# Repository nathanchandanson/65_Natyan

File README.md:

# 65_Natyan

The 65_Natyan is a custom 65% mechanical keyboard. It has individually addressable SK6812 led under each key. It is hotswappable and support both Cherry MX and Kailh Choc switches.

# Work in progress

This project is currently being developed, thus it is not sure that all will work.

## PCB

The Kicad project is accessible in the folder "pcb_files". You can open it to export the GERBER files and then order the PCB.

## Firmware

The firmware is based on [qmk_firmware](https://github.com/qmk/qmk_firmware). To flash the firmware, just follow the instructions given on the QMK docs.

## 3dModels

You can find the 3d models of the case I designed for this keyboard. 
To get it, you need to 3d print them, and wherever there is a hole for a fastener, you need to install a heat-press insert.

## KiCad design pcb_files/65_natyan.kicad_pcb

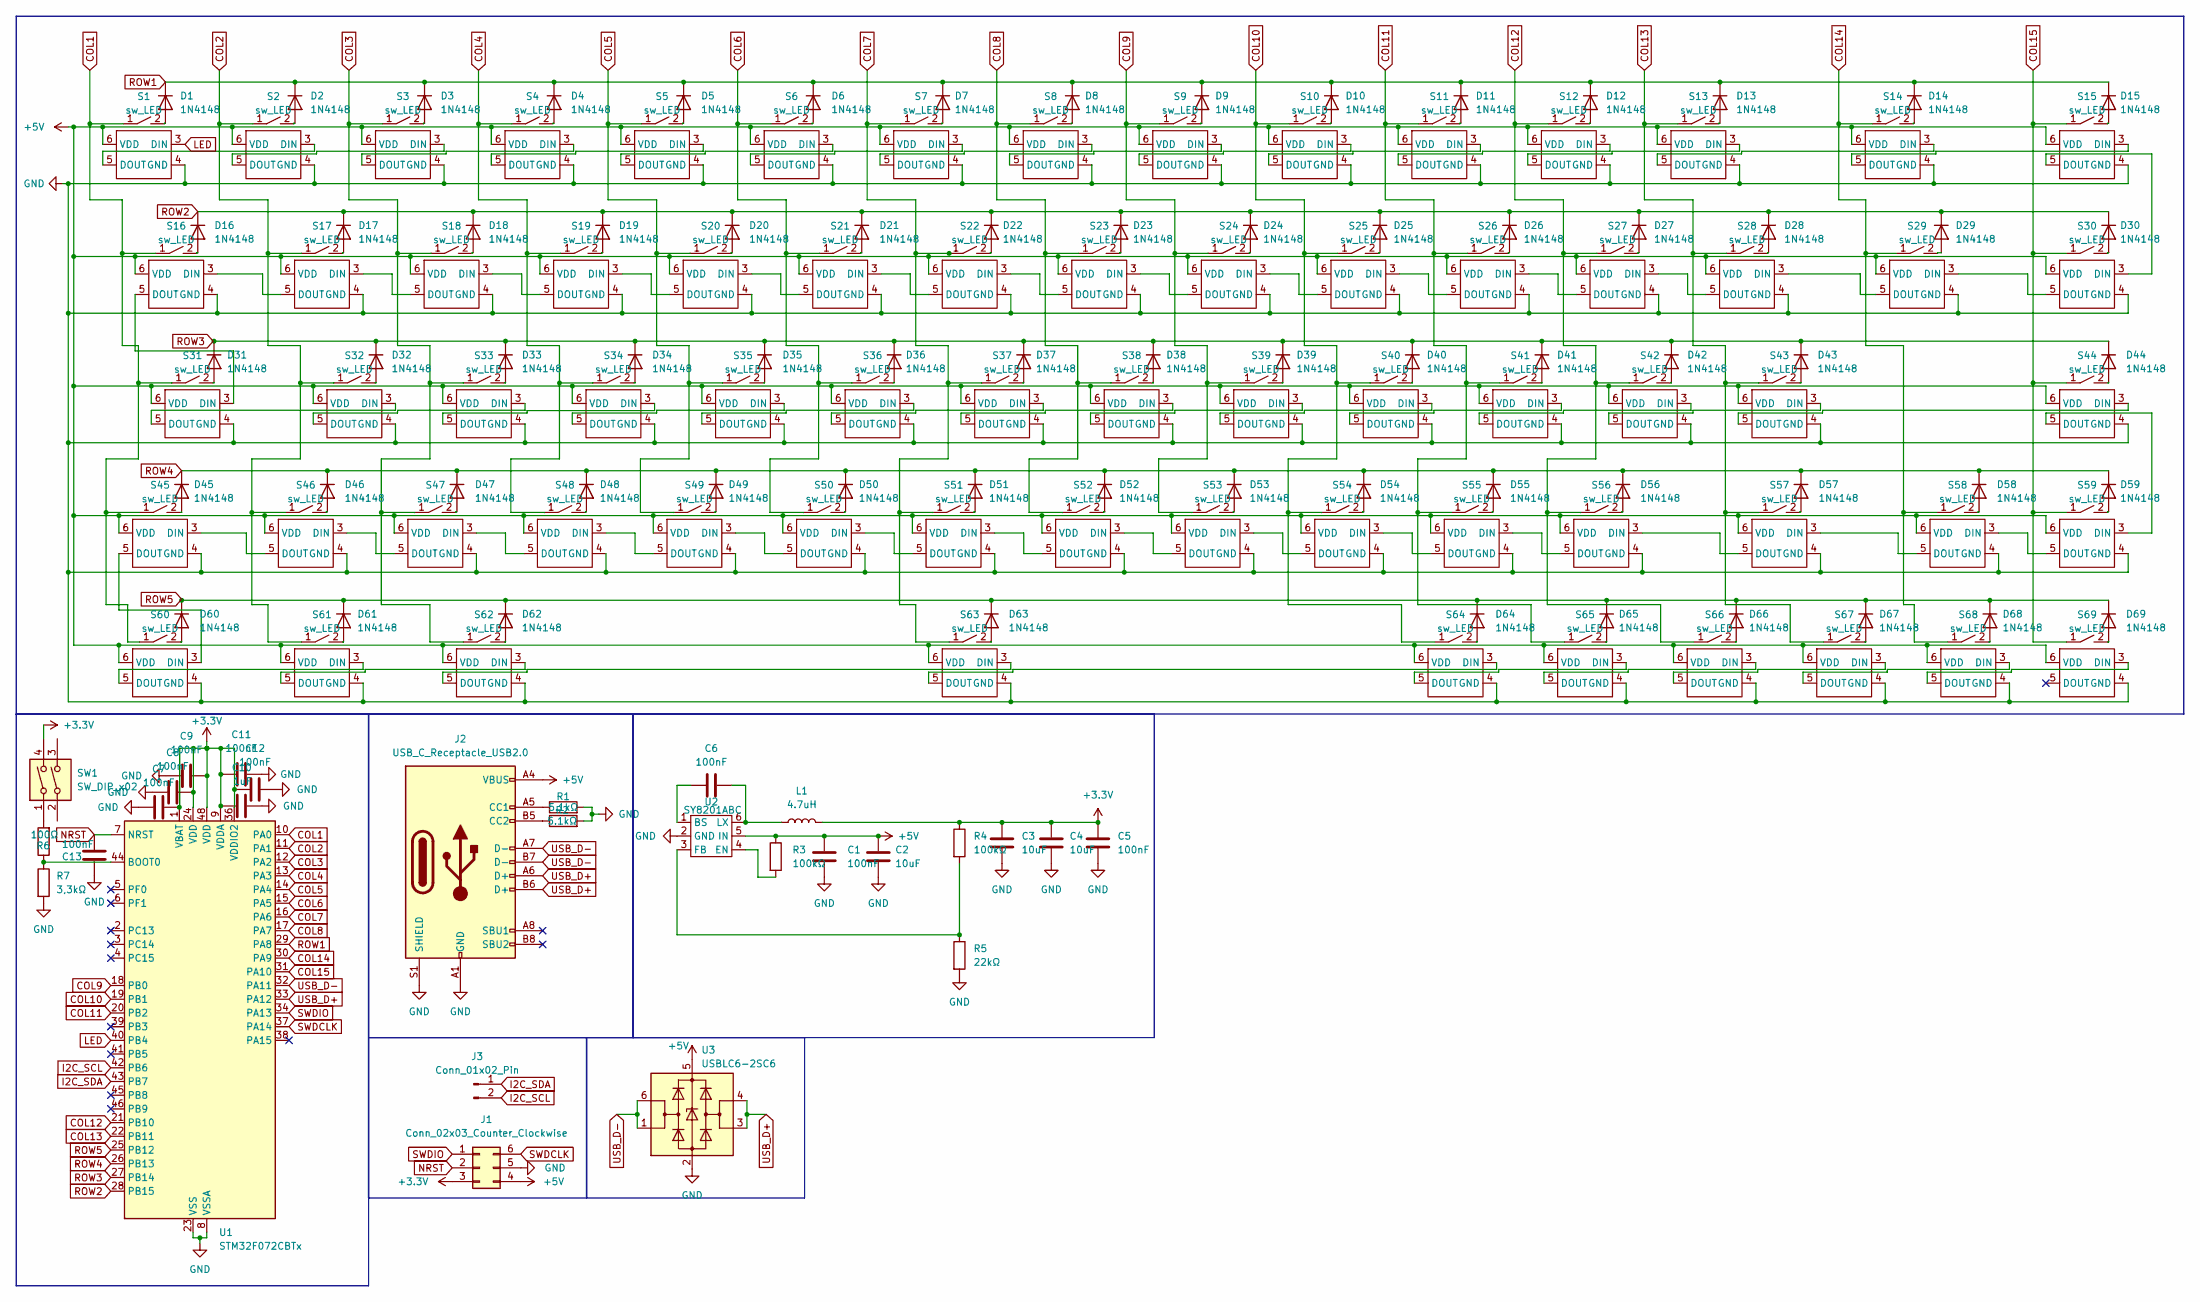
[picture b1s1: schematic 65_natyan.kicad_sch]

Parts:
C1, C5, C6, C7, C8, C9, C11, C12, C13: 100nF; C_0603_1608Metric_Pad1.08x0.95mm_HandSolder
C2, C3, C4: 10uF; C_0603_1608Metric_Pad1.08x0.95mm_HandSolder
C10: 1uF; C_0603_1608Metric_Pad1.08x0.95mm_HandSolder
D1, D2, D3, D4, D5, D6, D7, D8, D9, D10, D11, D12, D13, D14, D15, D16, D17, D18, D19, D20, D21, D22, D23, D24, D25, D26, D27, D28, D29, D30, D31, D32, D33, D34, D35, D36, D37, D38, D39, D40, D41, D42, D43, D44, D45, D46, D47, D48, D49, D50, D51, D52, D53, D54, D55, D56, D57, D58, D59, D60, D61, D62, D63, D64, D65, D66, D67, D68, D69: 1N4148; D_DO-35_SOD27_P7.62mm_Horizontal
J1: Conn_02x03_Counter_Clockwise; PinHeader_2x03_P2.54mm_Vertical
J2: USB_C_Receptacle_USB2.0; USB-C-SMD_KH-TYPE-C-16P
J3: Conn_01x02_Pin; PinHeader_1x02_P2.54mm_Vertical
L1: 4.7uH; L_0603_1608Metric_Pad1.05x0.95mm_HandSolder
R1, R2: 5.1kΩ; R_0603_1608Metric_Pad0.98x0.95mm_HandSolder
R3, R4: 100kΩ; R_0603_1608Metric_Pad0.98x0.95mm_HandSolder
R5: 22kΩ; R_0603_1608Metric_Pad0.98x0.95mm_HandSolder
R6: 100Ω; R_0603_1608Metric_Pad0.98x0.95mm_HandSolder
R7: 3,3kΩ; R_0603_1608Metric_Pad0.98x0.95mm_HandSolder
S1, S2, S3, S4, S5, S6, S7, S8, S9, S10, S11, S12, S13, S15, S17, S18, S19, S20, S21, S22, S23, S24, S25, S26, S27, S28, S30, S32, S33, S34, S35, S36, S37, S38, S39, S40, S41, S42, S43, S44, S46, S47, S48, S49, S50, S51, S52, S53, S54, S55, S56, S58, S59, S64, S65, S66, S67, S68, S69: sw_LED; sw_MX-Choc_Hotswap-underLED_1u
S14: sw_LED; sw_MX-Choc_Hotswap-underLED_2u
S16: sw_LED; sw_MX-Choc_Hotswap-underLED_1.5u
S29: sw_LED; sw_MX-Choc_Hotswap-underLED_isoEnter
S31, S57: sw_LED; sw_MX-Choc_Hotswap-underLED_1.75u
S45, S60, S61, S62: sw_LED; sw_MX-Choc_Hotswap-underLED_1.25u
S63: sw_LED; sw_MX-Choc_Hotswap-underLED_6,25u
SW1: SW_DIP_x02; rst_sw
U1: STM32F072CBTx; LQFP-48_7x7mm_P0.5mm
U2: SY8201ABC; SOT-23-6_Handsoldering
U3: USBLC6-2SC6; SOT-23-6_Handsoldering

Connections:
+3.3V: C3.1, C4.1, C5.1, C7.2, C8.1, C9.2, C10.1, C11.1, C12.1, J1.3, L1.2, R4.1, SW1.4, U1.1 (VBAT), U1.9 (VDDA), U1.24 (VDD), U1.36 (VDDIO2), U1.48 (VDD)
+5V: C1.1, C2.1, J1.4, J2.A4 (VBUS), J2.A9 (VBUS), J2.B4 (VBUS), J2.B9 (VBUS), R3.1, S1.6 (VDD), S2.6 (VDD), S3.6 (VDD), S4.6 (VDD), S5.6 (VDD), S6.6 (VDD), S7.6 (VDD), S8.6 (VDD), S9.6 (VDD), S10.6 (VDD), S11.6 (VDD), S12.6 (VDD), S13.6 (VDD), S14.6 (VDD), S15.6 (VDD), S16.6 (VDD), S17.6 (VDD), S18.6 (VDD), S19.6 (VDD), S20.6 (VDD), S21.6 (VDD), S22.6 (VDD), S23.6 (VDD), S24.6 (VDD), S25.6 (VDD), S26.6 (VDD), S27.6 (VDD), S28.6 (VDD), S29.6 (VDD), S30.6 (VDD), S31.6 (VDD), S32.6 (VDD), S33.6 (VDD), S34.6 (VDD), S35.6 (VDD), S36.6 (VDD), S37.6 (VDD), S38.6 (VDD), S39.6 (VDD), S40.6 (VDD), S41.6 (VDD), S42.6 (VDD), S43.6 (VDD), S44.6 (VDD), S45.6 (VDD), S46.6 (VDD), S47.6 (VDD), S48.6 (VDD), S49.6 (VDD), S50.6 (VDD), S51.6 (VDD), S52.6 (VDD), S53.6 (VDD), S54.6 (VDD), S55.6 (VDD), S56.6 (VDD), S57.6 (VDD), S58.6 (VDD), S59.6 (VDD), S60.6 (VDD), S61.6 (VDD), S62.6 (VDD), S63.6 (VDD), S64.6 (VDD), S65.6 (VDD), S66.6 (VDD), S67.6 (VDD), S68.6 (VDD), S69.6 (VDD), U2.5 (IN), U3.5 (VBUS)
COL1: S1.1, S16.1, S31.1, S45.1, S60.1, U1.10 (PA0)
COL2: S2.1, S17.1, S32.1, S46.1, S61.1, U1.11 (PA1)
COL3: S3.1, S18.1, S33.1, S47.1, S62.1, U1.12 (PA2)
COL4: S4.1, S19.1, S34.1, S48.1, U1.13 (PA3)
COL5: S5.1, S20.1, S35.1, S49.1, U1.14 (PA4)
COL6: S6.1, S21.1, S36.1, S50.1, U1.15 (PA5)
COL7: S7.1, S22.1, S37.1, S51.1, S63.1, U1.16 (PA6)
COL8: S8.1, S23.1, S38.1, S52.1, U1.17 (PA7)
COL9: S9.1, S24.1, S39.1, S53.1, U1.18 (PB0)
COL10: S10.1, S25.1, S40.1, S54.1, S64.1, U1.19 (PB1)
COL11: S11.1, S26.1, S41.1, S55.1, S65.1, U1.20 (PB2)
COL12: S12.1, S27.1, S42.1, S56.1, S66.1, U1.21 (PB10)
COL13: S13.1, S28.1, S43.1, S57.1, S67.1, U1.22 (PB11)
COL14: S14.1, S29.1, S58.1, S68.1, U1.30 (PA9)
COL15: S15.1, S30.1, S44.1, S59.1, S69.1, U1.31 (PA10)
GND: C1.2, C2.2, C3.2, C4.2, C5.2, C7.1, C8.2, C9.1, C10.2, C11.2, C12.2, C13.1, J1.5, J2.A1 (GND), J2.A12 (GND), J2.B1 (GND), J2.B12 (GND), J2.S1 (SHIELD), R1.2, R2.2, R5.2, R7.2, S1.4 (GND), S2.4 (GND), S3.4 (GND), S4.4 (GND), S5.4 (GND), S6.4 (GND), S7.4 (GND), S8.4 (GND), S9.4 (GND), S10.4 (GND), S11.4 (GND), S12.4 (GND), S13.4 (GND), S14.4 (GND), S15.4 (GND), S16.4 (GND), S17.4 (GND), S18.4 (GND), S19.4 (GND), S20.4 (GND), S21.4 (GND), S22.4 (GND), S23.4 (GND), S24.4 (GND), S25.4 (GND), S26.4 (GND), S27.4 (GND), S28.4 (GND), S29.4 (GND), S30.4 (GND), S31.4 (GND), S32.4 (GND), S33.4 (GND), S34.4 (GND), S35.4 (GND), S36.4 (GND), S37.4 (GND), S38.4 (GND), S39.4 (GND), S40.4 (GND), S41.4 (GND), S42.4 (GND), S43.4 (GND), S44.4 (GND), S45.4 (GND), S46.4 (GND), S47.4 (GND), S48.4 (GND), S49.4 (GND), S50.4 (GND), S51.4 (GND), S52.4 (GND), S53.4 (GND), S54.4 (GND), S55.4 (GND), S56.4 (GND), S57.4 (GND), S58.4 (GND), S59.4 (GND), S60.4 (GND), S61.4 (GND), S62.4 (GND), S63.4 (GND), S64.4 (GND), S65.4 (GND), S66.4 (GND), S67.4 (GND), S68.4 (GND), S69.4 (GND), U1.8 (VSSA), U1.23 (VSS), U1.35 (VSS), U1.47 (VSS), U2.2 (GND), U3.2 (GND)
I2C_SCL: J3.2, U1.42 (PB6)
I2C_SDA: J3.1, U1.43 (PB7)
LED: S1.3 (DIN), U1.40 (PB4)
NRST: C13.2, J1.2, U1.7 (NRST)
unnamed: D1.2 (A), S1.2
unnamed: D2.2 (A), S2.2
unnamed: D3.2 (A), S3.2
unnamed: D4.2 (A), S4.2
unnamed: D5.2 (A), S5.2
unnamed: D6.2 (A), S6.2
unnamed: D7.2 (A), S7.2
unnamed: D8.2 (A), S8.2
unnamed: D9.2 (A), S9.2
unnamed: D10.2 (A), S10.2
unnamed: D11.2 (A), S11.2
unnamed: D12.2 (A), S12.2
unnamed: D13.2 (A), S13.2
unnamed: D14.2 (A), S14.2
unnamed: D15.2 (A), S15.2
unnamed: D16.2 (A), S16.2
unnamed: D17.2 (A), S17.2
unnamed: D18.2 (A), S18.2
unnamed: D19.2 (A), S19.2
unnamed: D20.2 (A), S20.2
unnamed: D21.2 (A), S21.2
unnamed: D22.2 (A), S22.2
unnamed: D23.2 (A), S23.2
unnamed: D24.2 (A), S24.2
unnamed: D25.2 (A), S25.2
unnamed: D26.2 (A), S26.2
unnamed: D27.2 (A), S27.2
unnamed: D28.2 (A), S28.2
unnamed: D29.2 (A), S29.2
unnamed: D30.2 (A), S30.2
unnamed: D31.2 (A), S31.2
unnamed: D32.2 (A), S32.2
unnamed: D33.2 (A), S33.2
unnamed: D34.2 (A), S34.2
unnamed: D35.2 (A), S35.2
unnamed: D36.2 (A), S36.2
unnamed: D37.2 (A), S37.2
unnamed: D38.2 (A), S38.2
unnamed: D39.2 (A), S39.2
unnamed: D40.2 (A), S40.2
unnamed: D41.2 (A), S41.2
unnamed: D42.2 (A), S42.2
unnamed: D43.2 (A), S43.2
unnamed: D44.2 (A), S44.2
unnamed: D45.2 (A), S45.2
unnamed: D46.2 (A), S46.2
unnamed: D47.2 (A), S47.2
unnamed: D48.2 (A), S48.2
unnamed: D49.2 (A), S49.2
unnamed: D50.2 (A), S50.2
unnamed: D51.2 (A), S51.2
unnamed: D52.2 (A), S52.2
unnamed: D53.2 (A), S53.2
unnamed: D54.2 (A), S54.2
unnamed: D55.2 (A), S55.2
unnamed: D56.2 (A), S56.2
unnamed: D57.2 (A), S57.2
unnamed: D58.2 (A), S58.2
unnamed: D59.2 (A), S59.2
unnamed: D60.2 (A), S60.2
unnamed: D61.2 (A), S61.2
unnamed: D62.2 (A), S62.2
unnamed: D63.2 (A), S63.2
unnamed: D64.2 (A), S64.2
unnamed: D65.2 (A), S65.2
unnamed: D66.2 (A), S66.2
unnamed: D67.2 (A), S67.2
unnamed: D68.2 (A), S68.2
unnamed: D69.2 (A), S69.2
unnamed: J2.A5 (CC1), R1.1
unnamed: J2.B5 (CC2), R2.1
unnamed: R6.2, SW1.1
unnamed: S1.5 (DOUT), S2.3 (DIN)
unnamed: S2.5 (DOUT), S3.3 (DIN)
unnamed: S3.5 (DOUT), S4.3 (DIN)
unnamed: S4.5 (DOUT), S5.3 (DIN)
unnamed: S5.5 (DOUT), S6.3 (DIN)
unnamed: S6.5 (DOUT), S7.3 (DIN)
unnamed: S7.5 (DOUT), S8.3 (DIN)
unnamed: S8.5 (DOUT), S9.3 (DIN)
unnamed: S9.5 (DOUT), S10.3 (DIN)
unnamed: S10.5 (DOUT), S11.3 (DIN)
unnamed: S11.5 (DOUT), S12.3 (DIN)
unnamed: S12.5 (DOUT), S13.3 (DIN)
unnamed: S13.5 (DOUT), S14.3 (DIN)
unnamed: S14.5 (DOUT), S15.3 (DIN)
unnamed: S15.5 (DOUT), S30.3 (DIN)
unnamed: S16.3 (DIN), S17.5 (DOUT)
unnamed: S16.5 (DOUT), S31.3 (DIN)
unnamed: S17.3 (DIN), S18.5 (DOUT)
unnamed: S18.3 (DIN), S19.5 (DOUT)
unnamed: S19.3 (DIN), S20.5 (DOUT)
unnamed: S20.3 (DIN), S21.5 (DOUT)
unnamed: S21.3 (DIN), S22.5 (DOUT)
unnamed: S22.3 (DIN), S23.5 (DOUT)
unnamed: S23.3 (DIN), S24.5 (DOUT)
unnamed: S24.3 (DIN), S25.5 (DOUT)
unnamed: S25.3 (DIN), S26.5 (DOUT)
unnamed: S26.3 (DIN), S27.5 (DOUT)
unnamed: S27.3 (DIN), S28.5 (DOUT)
unnamed: S28.3 (DIN), S29.5 (DOUT)
unnamed: S29.3 (DIN), S30.5 (DOUT)
unnamed: S31.5 (DOUT), S32.3 (DIN)
unnamed: S32.5 (DOUT), S33.3 (DIN)
unnamed: S33.5 (DOUT), S34.3 (DIN)
unnamed: S34.5 (DOUT), S35.3 (DIN)
unnamed: S35.5 (DOUT), S36.3 (DIN)
unnamed: S36.5 (DOUT), S37.3 (DIN)
unnamed: S37.5 (DOUT), S38.3 (DIN)
unnamed: S38.5 (DOUT), S39.3 (DIN)
unnamed: S39.5 (DOUT), S40.3 (DIN)
unnamed: S40.5 (DOUT), S41.3 (DIN)
unnamed: S41.5 (DOUT), S42.3 (DIN)
unnamed: S42.5 (DOUT), S43.3 (DIN)
unnamed: S43.5 (DOUT), S44.3 (DIN)
unnamed: S44.5 (DOUT), S59.3 (DIN)
unnamed: S45.3 (DIN), S46.5 (DOUT)
unnamed: S45.5 (DOUT), S60.3 (DIN)
unnamed: S46.3 (DIN), S47.5 (DOUT)
unnamed: S47.3 (DIN), S48.5 (DOUT)
unnamed: S48.3 (DIN), S49.5 (DOUT)
unnamed: S49.3 (DIN), S50.5 (DOUT)
unnamed: S50.3 (DIN), S51.5 (DOUT)
unnamed: S51.3 (DIN), S52.5 (DOUT)
unnamed: S52.3 (DIN), S53.5 (DOUT)
unnamed: S53.3 (DIN), S54.5 (DOUT)
unnamed: S54.3 (DIN), S55.5 (DOUT)
unnamed: S55.3 (DIN), S56.5 (DOUT)
unnamed: S56.3 (DIN), S57.5 (DOUT)
unnamed: S57.3 (DIN), S58.5 (DOUT)
unnamed: S58.3 (DIN), S59.5 (DOUT)
unnamed: S60.5 (DOUT), S61.3 (DIN)
unnamed: S61.5 (DOUT), S62.3 (DIN)
unnamed: S62.5 (DOUT), S63.3 (DIN)
unnamed: S63.5 (DOUT), S64.3 (DIN)
unnamed: S64.5 (DOUT), S65.3 (DIN)
unnamed: S65.5 (DOUT), S66.3 (DIN)
unnamed: S66.5 (DOUT), S67.3 (DIN)
unnamed: S67.5 (DOUT), S68.3 (DIN)
unnamed: S68.5 (DOUT), S69.3 (DIN)
unnamed: R6.1, R7.1, U1.44 (BOOT0)
unnamed: C6.1, U2.1 (BS)
unnamed: R3.2, U2.4 (EN)
unnamed: R4.2, R5.1, U2.3 (FB)
unnamed: C6.2, L1.1, U2.6 (LX)
ROW1: D1.1 (K), D2.1 (K), D3.1 (K), D4.1 (K), D5.1 (K), D6.1 (K), D7.1 (K), D8.1 (K), D9.1 (K), D10.1 (K), D11.1 (K), D12.1 (K), D13.1 (K), D14.1 (K), D15.1 (K), U1.29 (PA8)
ROW2: D16.1 (K), D17.1 (K), D18.1 (K), D19.1 (K), D20.1 (K), D21.1 (K), D22.1 (K), D23.1 (K), D24.1 (K), D25.1 (K), D26.1 (K), D27.1 (K), D28.1 (K), D29.1 (K), D30.1 (K), U1.28 (PB15)
ROW3: D31.1 (K), D32.1 (K), D33.1 (K), D34.1 (K), D35.1 (K), D36.1 (K), D37.1 (K), D38.1 (K), D39.1 (K), D40.1 (K), D41.1 (K), D42.1 (K), D43.1 (K), D44.1 (K), U1.27 (PB14)
ROW4: D45.1 (K), D46.1 (K), D47.1 (K), D48.1 (K), D49.1 (K), D50.1 (K), D51.1 (K), D52.1 (K), D53.1 (K), D54.1 (K), D55.1 (K), D56.1 (K), D57.1 (K), D58.1 (K), D59.1 (K), U1.26 (PB13)
ROW5: D60.1 (K), D61.1 (K), D62.1 (K), D63.1 (K), D64.1 (K), D65.1 (K), D66.1 (K), D67.1 (K), D68.1 (K), D69.1 (K), U1.25 (PB12)
SWDCLK: J1.6, U1.37 (PA14)
SWDIO: J1.1, U1.34 (PA13)
USB_D+: J2.A6 (D+), J2.B6 (D+), U1.33 (PA12), U3.3 (I/O2), U3.4 (I/O2)
USB_D-: J2.A7 (D-), J2.B7 (D-), U1.32 (PA11), U3.1 (I/O1), U3.6 (I/O1)

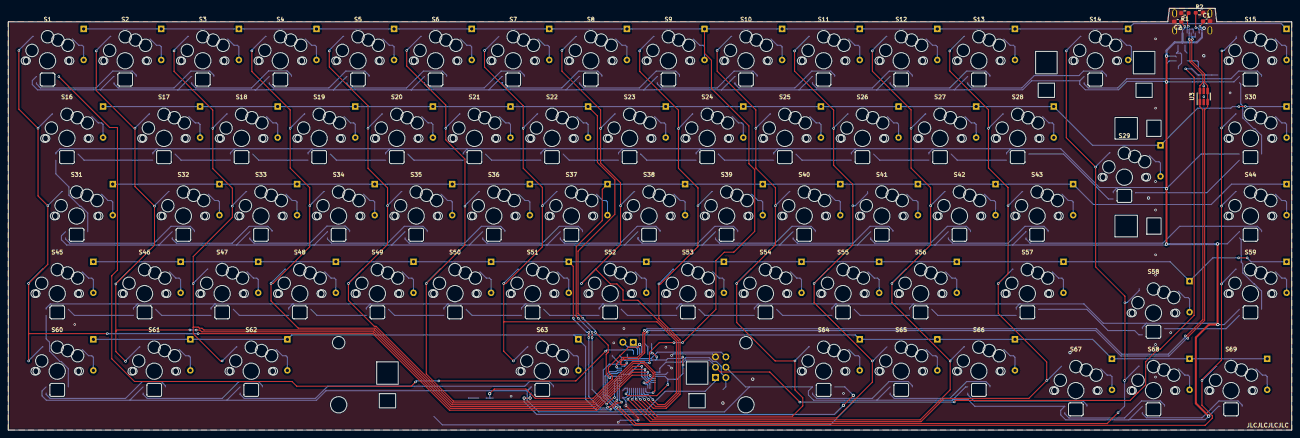
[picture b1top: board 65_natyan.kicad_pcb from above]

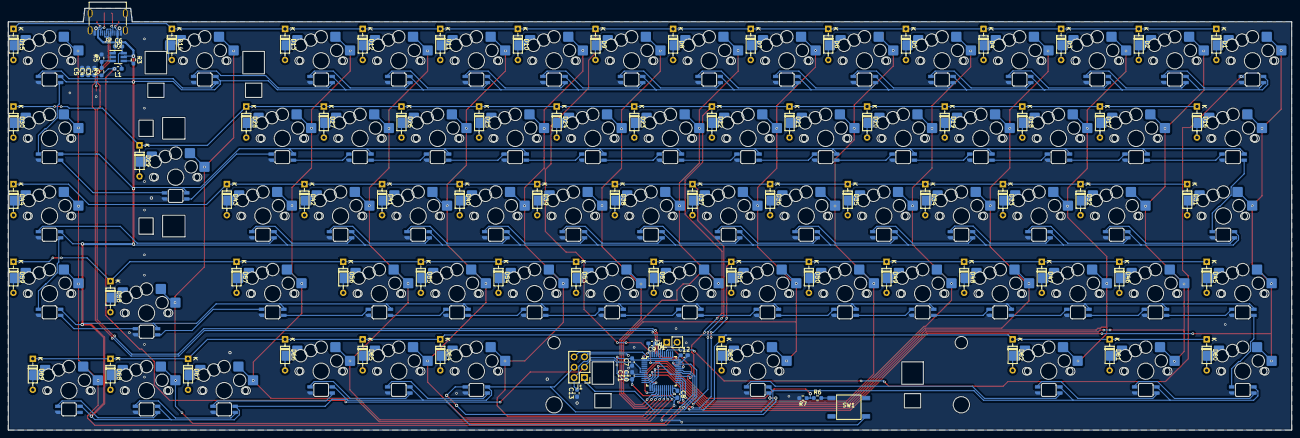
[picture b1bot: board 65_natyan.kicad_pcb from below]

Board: 2 copper layers, 315.0 x 103.5 mm, 166 parts (92 on the bottom side), 176 nets.

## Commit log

2024-09-06 Create README.md
    Added a README
2024-09-06 Create .gitignore
    Added .gitignore
2024-09-06 PCB files
    Added the Kicad project files.
2025-02-16 Added the base of the firmware
2025-03-20 First base implementation in the firmware
2025-03-21 Added VIAL support
2025-06-15 Added the 3d models for the non standard keycaps
2025-06-15 Added the 3d files for the case of the keyboard
2025-09-29 Updated version of keycaps
2025-09-29 Added the footprint libraries
